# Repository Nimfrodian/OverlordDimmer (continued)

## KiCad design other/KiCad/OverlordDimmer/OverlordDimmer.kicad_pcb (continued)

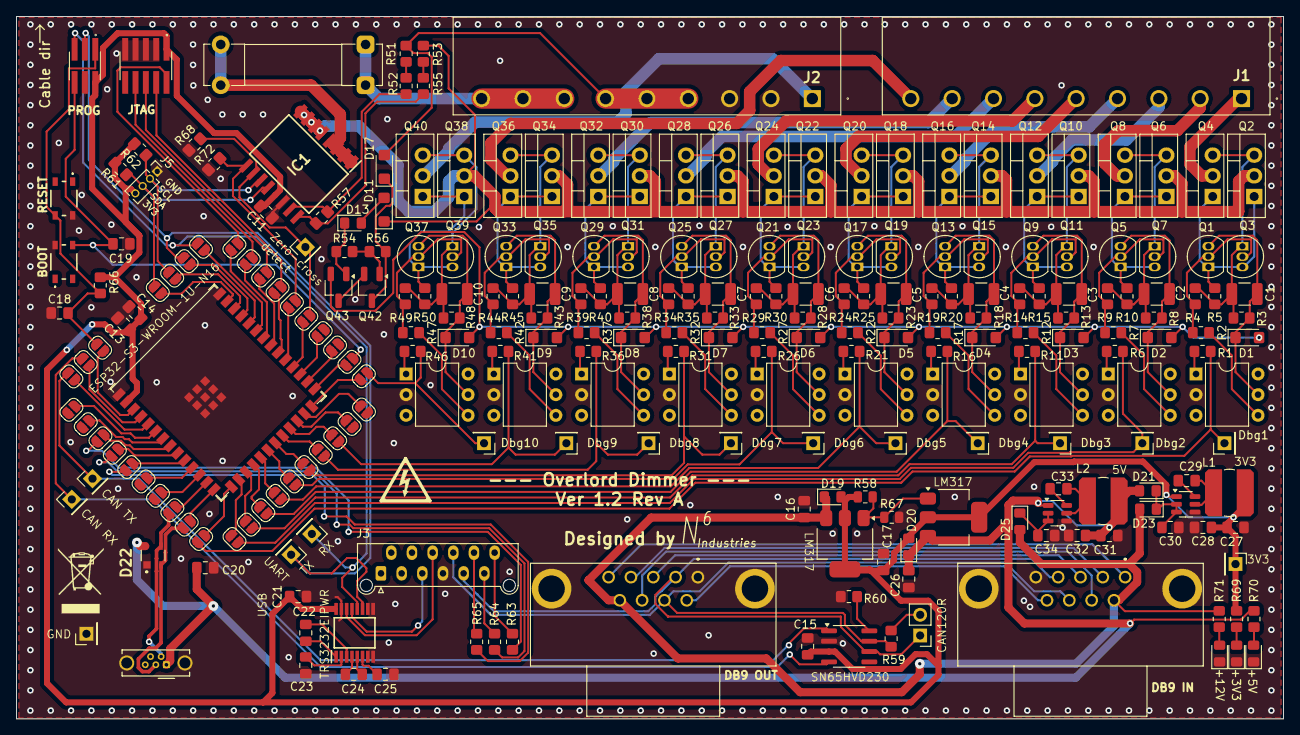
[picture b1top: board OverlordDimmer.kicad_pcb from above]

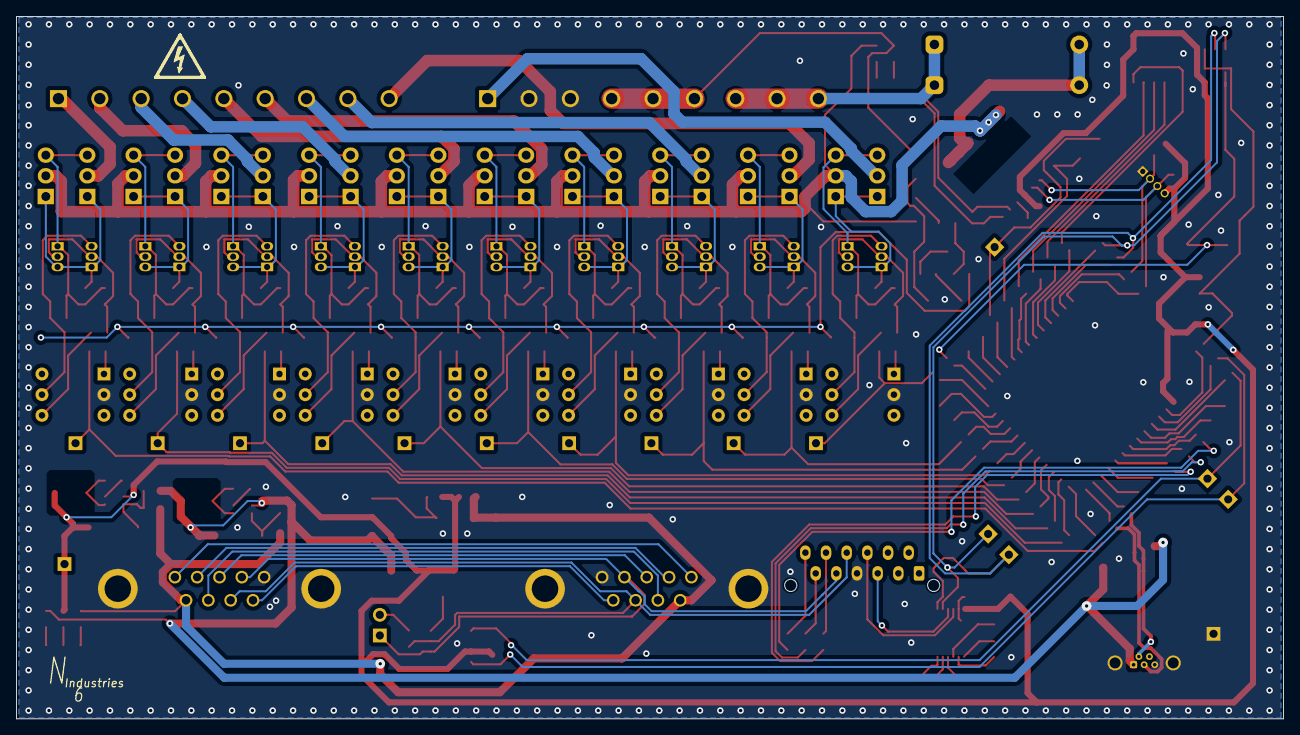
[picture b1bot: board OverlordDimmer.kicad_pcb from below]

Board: 2 copper layers, 155.7 x 86.3 mm, 261 parts (2 on the bottom side), 184 nets.

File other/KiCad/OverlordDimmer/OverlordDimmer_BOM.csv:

Reference,Value,Datasheet,Footprint,Qty,DNP
"BOOT1,RESET1",PTS810SJK250SMTR LFS,https://eu.mouser.com/ProductDetail/CK/PTS810SJK250SMTR-LFS?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,OverlordCommon:PTS810SJK250SMTRLFS,2,
"C1,C2,C3,C4,C5,C6,C7,C8,C9,C10",4.7u,https://eu.mouser.com/ProductDetail/Murata-Electronics/GRM32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,Capacitor_SMD:C_1210_3225Metric_Pad1.33x2.70mm_HandSolder,10,
"C11,C14",10uF,https://eu.mouser.com/ProductDetail/Samsung-Electro-Mechanic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,Capacitor_SMD:C_0805_2012Metric_Pad1.18x1.45mm_HandSolder,2,
C12,1nF,https://www.mouser.se/ProductDetail/Samsung-Electro-Mechanic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,Capacitor_SMD:C_0805_2012Metric_Pad1.18x1.45mm_HandSolder,1,
"C13,C15,C18,C19,C20,C21,C22,C23,C24,C25",0.1uF,https://eu.mouser.com/ProductDetail/KYOCERA-AVX/08053C104KAT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,Capacitor_SMD:C_0805_2012Metric_Pad1.18x1.45mm_HandSolder,10,
"C16,C17",1uF,https://eu.mouser.com/ProductDetail/KYOCERA-AVX/KGM21AR71E10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,Capacitor_SMD:C_0805_2012Metric_Pad1.18x1.45mm_HandSolder,2,
"D1,D2,D3,D4,D5,D6,D7,D8,D9,D10,D11,D17",VISHAY S07J-GS08,https://si.farnell.com/vishay/s07j-gs08/diode-switching-do21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,Diode_SMD:D_SMF,12,
"D12,D14,D15,D16,D18,D19,D20,D21",1N4148,https://www.mouser.se/ProductDetail/Taiwan-Semiconductor/TS4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,Diode_SMD:D_0805_2012Metric_Pad1.15x1.40mm_HandSolder,8,
D13,Unknown,https://eu.mouser.com/ProductDetail/Taiwan-Semiconductor/BZY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,Diode_SMD:D_0805_2012Metric_Pad1.15x1.40mm_HandSolder,1,
D22,TPD2E001DZDR,https://eu.mouser.com/ProductDetail/Texas-Instruments/TPD2E0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,OverlordCommon:TPD2E001DZDR,1,
DB9_IN1,5788792-2,https://eu.mouser.com/ProductDetail/TE-Connectivity/5788792-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,OverlordCommon:5788792,1,
DB9_OUT1,5747844-4,https://eu.mouser.com/ProductDetail/TE-Connectivity/5747844-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,OverlordCommon:57478444,1,
"Dbg1,Dbg2,Dbg3,Dbg3V3_1,Dbg4,Dbg5,Dbg6,Dbg7,Dbg8,Dbg9,Dbg10,DbgCRX1,DbgCTX1,DbgEdge1,DbgGND1,DbgURX1,DbgUTX1",Connector_Conn_01x01_Male,,Connector_PinHeader_2.54mm:PinHeader_1x01_P2.54mm_Vertical,17,
"J1,J2",1757310,http://www.phoenixcontact.com/de/produkte/1757310/pdf,OverlordCommon:1757310,2,
J3,Conn_01x12_Pin,https://www.mouser.se/ProductDetail/538-90325-0012,Connector_Molex:Molex_Picoflex_90325-0012_2x06_P1.27mm_Vertical,1,
J_CAN120R1,Conn_01x02_Male,~,Connector_PinHeader_2.54mm:PinHeader_1x02_P2.54mm_Vertical,1,
J_JTAG1,FTSH-105-01-S-DV-K,https://eu.mouser.com/ProductDetail/Samtec/FTSH-105-01-S-DV-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,OverlordCommon:FTSH-105-XX-YYY-DV-K,1,
"J_JTAG3V3_1,J_PROG3V3_1",Conn_01x02_Pin,~,Connector_PinHeader_2.54mm:PinHeader_1x02_P2.54mm_Vertical,2,
J_PROG1,FTSH-103-01-S-DV-TR,https://eu.mouser.com/ProductDetail/Samtec/FTSH-103-01-S-DV-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,OverlordCommon:FTSH-103-XX-YYY-DV-TR,1,
J_USB1,USB_B,https://si.farnell.com/1321918?CMP=e-email-sys-shipping-GLB-Product,Connector_USB:USB_B_Lumberg_2411_02_Horizontal,1,
"Q1,Q5,Q9,Q13,Q17,Q21,Q25,Q29,Q33,Q37",2N3904,https://si.farnell.com/multicomp/2n3904/transistor-npn-to-92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,Package_TO_SOT_THT:TO-92_Inline,10,
"Q2,Q4,Q6,Q8,Q10,Q12,Q14,Q16,Q18,Q20,Q22,Q24,Q26,Q28,Q30,Q32,Q34,Q36,Q38,Q40",IRF740,https://si.farnell.com/vishay/irf740bpbf/mosfet-n-ch-400v-10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,Package_TO_SOT_THT:TO-220-3_Vertical,20,
"Q3,Q7,Q11,Q15,Q19,Q23,Q27,Q31,Q35,Q39",2N3906,https://si.farnell.com/multicomp/2n3906/transistor-45v-200ma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,Package_TO_SOT_THT:TO-92_Inline,10,
Q41,BC817,https://si.farnell.com/1081223?CMP=e-email-sys-shipping-GLB-Product,Package_TO_SOT_SMD:SOT-23,1,
"Q42,Q43",2SC4061KT146N,https://si.farnell.com/rohm/2sc4061kt146n/trans-npn-300v-0-1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,Package_TO_SOT_SMD:SC-59_Handsoldering,2,
"R1,R6,R11,R16,R21,R26,R31,R36,R41,R46,R62,R63,R64",220,https://si.farnell.com/multicomp/mchvr06jtev2200/res-220r-5-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,Resistor_SMD:R_0805_2012Metric_Pad1.20x1.40mm_HandSolder,13,
"R2,R7,R12,R17,R22,R27,R32,R37,R42,R47,R53",1k,https://si.farnell.com/vishay/crcw08051k00jnea/res-1k-5-0-12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,Resistor_SMD:R_0805_2012Metric_Pad1.20x1.40mm_HandSolder,11,
"R3,R5,R8,R10,R13,R15,R18,R20,R23,R25,R28,R30,R33,R35,R38,R40,R43,R45,R48,R50",470k,https://si.farnell.com/multicomp/mcmr04x474-jtl/res-470k-5-0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,Resistor_SMD:R_0805_2012Metric_Pad1.20x1.40mm_HandSolder,20,
"R4,R9,R14,R19,R24,R29,R34,R39,R44,R49,R65",10k,https://si.farnell.com/vishay/crcw080510k0jneaif/res-10k-5-0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,Resistor_SMD:R_0805_2012Metric_Pad1.20x1.40mm_HandSolder,11,
"R51,R57",220k,https://www.mouser.se/ProductDetail/Bourns/CR0805-JW-224ELF?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,Resistor_SMD:R_0805_2012Metric_Pad1.20x1.40mm_HandSolder,2,
R52,2.2k,https://si.farnell.com/yageo/rc1210jr-072k2l/res-2k2-5-0-5w-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,Resistor_SMD:R_0805_2012Metric_Pad1.20x1.40mm_HandSolder,1,
R54,100k,https://si.farnell.com/te-connectivity/crgcq1210j100k/res-10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,Resistor_SMD:R_0805_2012Metric_Pad1.20x1.40mm_HandSolder,1,
R55,22k,https://si.farnell.com/te-connectivity/crgcq1210f22k/res-22k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,Resistor_SMD:R_0805_2012Metric_Pad1.20x1.40mm_HandSolder,1,
R56,75k,https://si.farnell.com/rohm/ktr25jzpf7502/res-75k-1-0-33w-12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,Resistor_SMD:R_0805_2012Metric_Pad1.20x1.40mm_HandSolder,1,
R58,240,https://www.mouser.se/ProductDetail/Vishay-Dale/CRCW0805240R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,Resistor_SMD:R_0805_2012Metric,1,
R59,120,https://si.farnell.com/multicomp/mcwr04x1200ftl/res-120r-1-0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,Resistor_SMD:R_0805_2012Metric_Pad1.20x1.40mm_HandSolder,1,
R60,0R,https://www.mouser.se/ProductDetail/Vishay-Dale/CRCW08050000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,Resistor_SMD:R_0805_2012Metric_Pad1.20x1.40mm_HandSolder,1,
R61,390,https://eu.mouser.com/ProductDetail/Panasonic/ERJ-P06F3900V?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,Resistor_SMD:R_0805_2012Metric,1,
"U1,U2,U3,U4,U5,U6,U7,U8,U9,U10",4N25,https://si.farnell.com/vishay/4n25/optocoupler-5kv-transisto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,Package_DIP:DIP-6_W7.62mm,10,
U11,SN65HVD230,https://si.farnell.com/texas-instruments/sn65hvd230dr/can-tr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,Package_SO:SOIC-8_3.9x4.9mm_P1.27mm,1,
U_4N35_1,4N35,https://www.mouser.se/ProductDetail/Vishay-Semiconductors/4N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,Package_DIP:DIP-6_W7.62mm,1,
U_ESP32-S3-WROOM-1U-N16_1,ESP32S3-Wroom,https://www.mouser.se/ProductDetail/Espressif-Systems/ESP32-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,PCM_Espressif:ESP32-S3-WROOM-1U,1,
U_LM317_1,LM317_SOT-223,https://www.mouser.se/ProductDetail/Texas-Instruments/LM317D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,Package_TO_SOT_SMD:SOT-223-3_TabPin2,1,
U_TRS3232EIPWR1,TRS3232EIPWR,https://eu.mouser.com/ProductDetail/Texas-Instruments/TRS323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,OverlordCommon:SOP65P640X120-16N,1,

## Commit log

2023-12-13 Main version
2023-12-13 added minimum time as the circuit is expected to trigger some microseconds early
2023-12-15 implemented triggering delay as the detection circuit fires early (before actual zero-cross)
2023-12-15 added re-trigger guard
2024-06-23 Added waveforms project
2024-06-29 Reworked PCB for NMOS, i.e., trailing edge
2024-07-06 Finalised ver1.0 revA of PCB
2024-07-06 Added gerber files
2024-07-12 Rewrote for mosfet, but not 100% reliable, WIP
2024-07-20 Rework for mosfet control, added unit testing (TODO: implement debugging of unit tests) TODO: - add dynamic adapting to changing cycle times
2024-07-23 Added period compensation code TODO: debug issue where if several outputs are 100% they are not active for a short time on zero-crossing
2024-08-03 pre-rewritte commit
2024-08-03 WIP added CAN message rework
2024-08-03 WIP further CAN message rework
2024-08-03 WIP added logic and table creation
2024-08-03 rework complete, triggering much more reliable
2024-08-06 Partial change to new naming convention
2024-08-07 added minimum delay time to fix issue with too small triggering delay resulting in no-turn-off behaviour
2024-08-09 replaced CAN module for espressif built-in twai module
2024-08-11 code cleanup, refactored code
2024-08-11 Added error handling module Updated test cases
2024-08-12 improved error handling errh 100% code coverage, unit tests pass
2024-08-12 Fixed TODOs
2024-08-12 code works TODO: add no-init guards to timing functions
2024-08-13 updated serial abstraction, minor code fixes
2024-08-13 added CAN reporting of errors TODO: implement ISR safe way of error reporting
2024-11-23 Final commit from laptop
2024-11-23 Added rtdb project as a submodule
2024-11-23 updated for latest rtdb_generator
2024-11-25 Updated for RTDB implementation and no-error on compilation
2024-11-25 Updated for RTDB project integration
2024-11-26 Finalized simple RTDB integration for initial test
2024-12-01 initial commit for DMAS functionality, WIP
2024-12-14 updated for debugging with esp-prog, improved DMAS
2025-01-12 Working AC dimming on bench
2025-01-18 uploadable code, serial communication OK TODO: check pin and functionality compatibility
2025-01-21 fixed GPIO timing
2025-01-29 Modified for S3 migration Prepared PCB for final inspection
2025-02-08 sent to production
2025-02-25 sent to production with fixes
2025-05-24 update to latest rtdb_gen
2025-05-25 added basic hardcoded remapping
2025-06-15 Sent for PCB production, ver 1.2 rev A
2025-08-27 Updated PCB design - added pullup on boot pin GPIO0 - schematic cleanup - removed unused power supply parts
2025-09-25 minor kicad changes
